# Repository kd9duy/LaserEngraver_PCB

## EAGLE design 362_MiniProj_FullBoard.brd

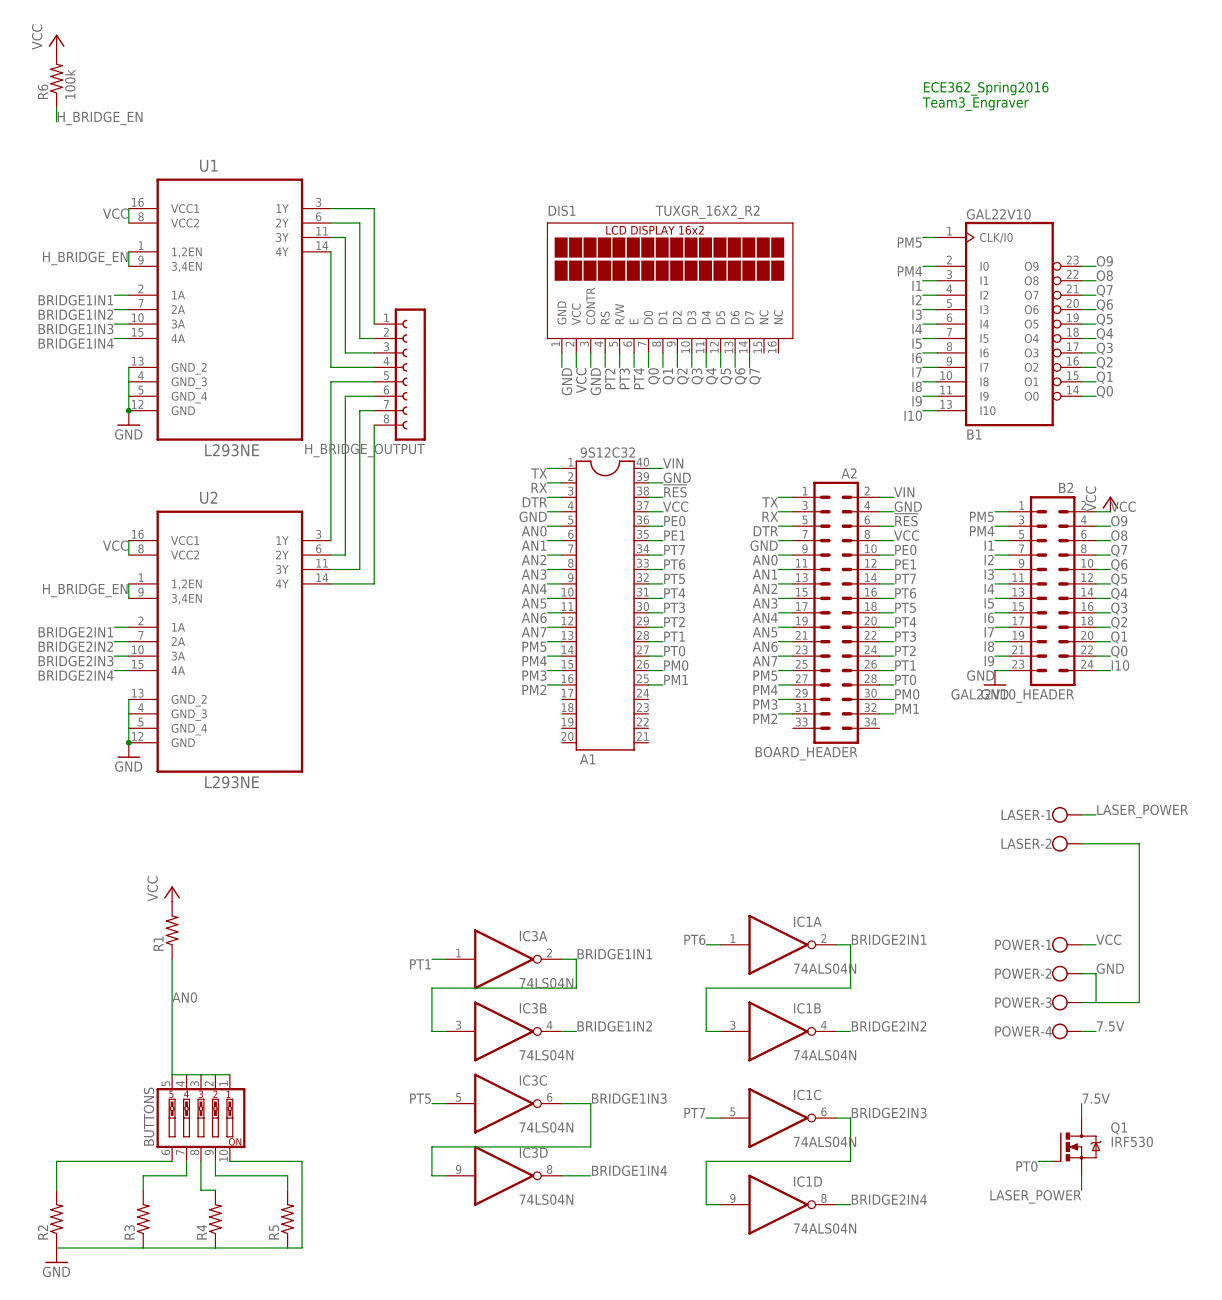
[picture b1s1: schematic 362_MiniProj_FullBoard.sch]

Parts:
9S12C32: A1; DIL40
BOARD_HEADER: A2; MA17-2
BUTTONS: SW_DIP-5; EDG-05
DIS1: TUXGR_16X2_R2
GAL22V10: B1; DIL24-3
GAL22V10_HEADER: B2; MA12-2
H_BRIDGE_OUTPUT: FE08-1; FE08
IC1: 74ALS04N; DIL14
IC3: 74LS04N; DIL14
LASER: W237-102
POWER: W239-104
Q1: IRF530; TO220BV
R1, R2, R3, R4, R5: R-US_0207/10; 0207/10
R6: 100k; 0207/10
U1, U2: L293NE; DIP254P762X508-16

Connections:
7.5V: POWER.4, Q1.D
!RES: 9S12C32.38, BOARD_HEADER.6
AN0: 9S12C32.5, BOARD_HEADER.9, BUTTONS.1, BUTTONS.2, BUTTONS.3, BUTTONS.4, BUTTONS.5, R1.1
AN1: 9S12C32.6, BOARD_HEADER.11
AN2: 9S12C32.7, BOARD_HEADER.13
AN3: 9S12C32.8, BOARD_HEADER.15
AN4: 9S12C32.9, BOARD_HEADER.17
AN5: 9S12C32.10, BOARD_HEADER.19
AN6: 9S12C32.11, BOARD_HEADER.21
AN7: 9S12C32.12, BOARD_HEADER.23
BRIDGE1IN1: IC3.2 (O), IC3.3 (I), U1.2 (1A)
BRIDGE1IN2: IC3.4 (O), U1.7 (2A)
BRIDGE1IN3: IC3.6 (O), IC3.9 (I), U1.10 (3A)
BRIDGE1IN4: IC3.8 (O), U1.15 (4A)
BRIDGE2IN1: IC1.2 (O), IC1.3 (I), U2.2 (1A)
BRIDGE2IN2: IC1.4 (O), U2.7 (2A)
BRIDGE2IN3: IC1.6 (O), IC1.9 (I), U2.10 (3A)
BRIDGE2IN4: IC1.8 (O), U2.15 (4A)
DTR: 9S12C32.3, BOARD_HEADER.5
GND: 9S12C32.4, 9S12C32.39, BOARD_HEADER.4, BOARD_HEADER.7, BUTTONS.10, DIS1.1 (GND), DIS1.3 (CONTR), GAL22V10.12 (GND), GAL22V10_HEADER.23, IC1.7 (GND), IC3.7 (GND), LASER.2, POWER.2, POWER.3, R2.1, R3.1, R4.1, R5.1, U1.4 (GND_3), U1.5 (GND_4), U1.12 (GND), U1.13 (GND_2), U2.4 (GND_3), U2.5 (GND_4), U2.12 (GND), U2.13 (GND_2)
H_BRIDGE_EN: R6.1, U1.1 (1,2EN), U1.9 (3,4EN), U2.1 (1,2EN), U2.9 (3,4EN)
I1: GAL22V10.3 (I1), GAL22V10_HEADER.5
I2: GAL22V10.4 (I2), GAL22V10_HEADER.7
I3: GAL22V10.5 (I3), GAL22V10_HEADER.9
I4: GAL22V10.6 (I4), GAL22V10_HEADER.11
I5: GAL22V10.7 (I5), GAL22V10_HEADER.13
I6: GAL22V10.8 (I6), GAL22V10_HEADER.15
I7: GAL22V10.9 (I7), GAL22V10_HEADER.17
I8: GAL22V10.10 (I8), GAL22V10_HEADER.19
I9: GAL22V10.11 (I9), GAL22V10_HEADER.21
I10: GAL22V10.13 (I10), GAL22V10_HEADER.24
LASER_POWER: LASER.1, Q1.S
unnamed: BUTTONS.6, R2.2
unnamed: BUTTONS.7, R3.2
unnamed: BUTTONS.8, R4.2
unnamed: BUTTONS.9, R5.2
unnamed: H_BRIDGE_OUTPUT.4, U1.14 (4Y)
unnamed: H_BRIDGE_OUTPUT.3, U1.11 (3Y)
unnamed: H_BRIDGE_OUTPUT.2, U1.6 (2Y)
unnamed: H_BRIDGE_OUTPUT.1, U1.3 (1Y)
unnamed: H_BRIDGE_OUTPUT.5, U2.3 (1Y)
unnamed: H_BRIDGE_OUTPUT.6, U2.6 (2Y)
unnamed: H_BRIDGE_OUTPUT.7, U2.11 (3Y)
unnamed: H_BRIDGE_OUTPUT.8, U2.14 (4Y)
O8: GAL22V10.22 (O8), GAL22V10_HEADER.6
O9: GAL22V10.23 (O9), GAL22V10_HEADER.4
PE0: 9S12C32.36, BOARD_HEADER.10
PE1: 9S12C32.35, BOARD_HEADER.12
PM0: 9S12C32.26, BOARD_HEADER.30
PM1: 9S12C32.25, BOARD_HEADER.32
PM2: 9S12C32.16, BOARD_HEADER.31
PM3: 9S12C32.15, BOARD_HEADER.29
PM4: 9S12C32.14, BOARD_HEADER.27, GAL22V10.2 (I0), GAL22V10_HEADER.3
PM5: 9S12C32.13, BOARD_HEADER.25, GAL22V10.1 (CLK/I0), GAL22V10_HEADER.1
PT0: 9S12C32.27, BOARD_HEADER.28, Q1.G
PT1: 9S12C32.28, BOARD_HEADER.26, IC3.1 (I)
PT2: 9S12C32.29, BOARD_HEADER.24, DIS1.4 (RS)
PT3: 9S12C32.30, BOARD_HEADER.22, DIS1.5 (R/W)
PT4: 9S12C32.31, BOARD_HEADER.20, DIS1.6 (E)
PT5: 9S12C32.32, BOARD_HEADER.18, IC3.5 (I)
PT6: 9S12C32.33, BOARD_HEADER.16, IC1.1 (I)
PT7: 9S12C32.34, BOARD_HEADER.14, IC1.5 (I)
Q0: DIS1.7 (D0), GAL22V10.14 (O0), GAL22V10_HEADER.22
Q1: DIS1.8 (D1), GAL22V10.15 (O1), GAL22V10_HEADER.20
Q2: DIS1.9 (D2), GAL22V10.16 (O2), GAL22V10_HEADER.18
Q3: DIS1.10 (D3), GAL22V10.17 (O3), GAL22V10_HEADER.16
Q4: DIS1.11 (D4), GAL22V10.18 (O4), GAL22V10_HEADER.14
Q5: DIS1.12 (D5), GAL22V10.19 (O5), GAL22V10_HEADER.12
Q6: DIS1.13 (D6), GAL22V10.20 (O6), GAL22V10_HEADER.10
Q7: DIS1.14 (D7), GAL22V10.21 (O7), GAL22V10_HEADER.8
RX: 9S12C32.2, BOARD_HEADER.3
TX: 9S12C32.1, BOARD_HEADER.1
VCC: 9S12C32.37, BOARD_HEADER.8, DIS1.2 (VCC), GAL22V10.24 (VCC), GAL22V10_HEADER.2, IC1.14 (VCC), IC3.14 (VCC), POWER.1, R1.2, R6.2, U1.8 (VCC2), U1.16 (VCC1), U2.8 (VCC2), U2.16 (VCC1)
VIN: 9S12C32.40, BOARD_HEADER.2

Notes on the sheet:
ECE362_Spring2016 Team3_Engraver

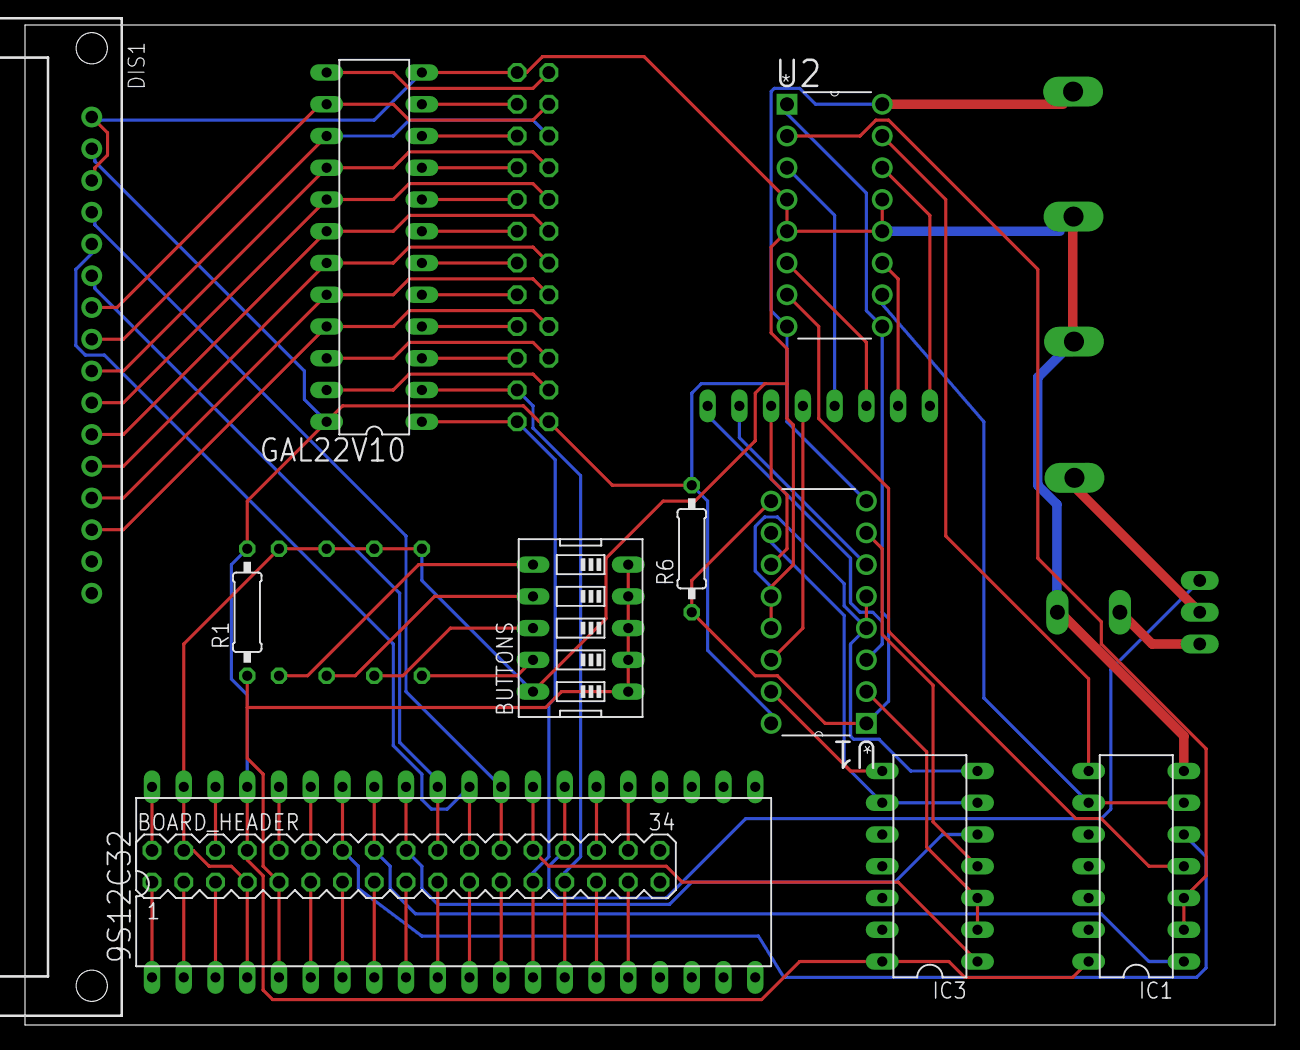
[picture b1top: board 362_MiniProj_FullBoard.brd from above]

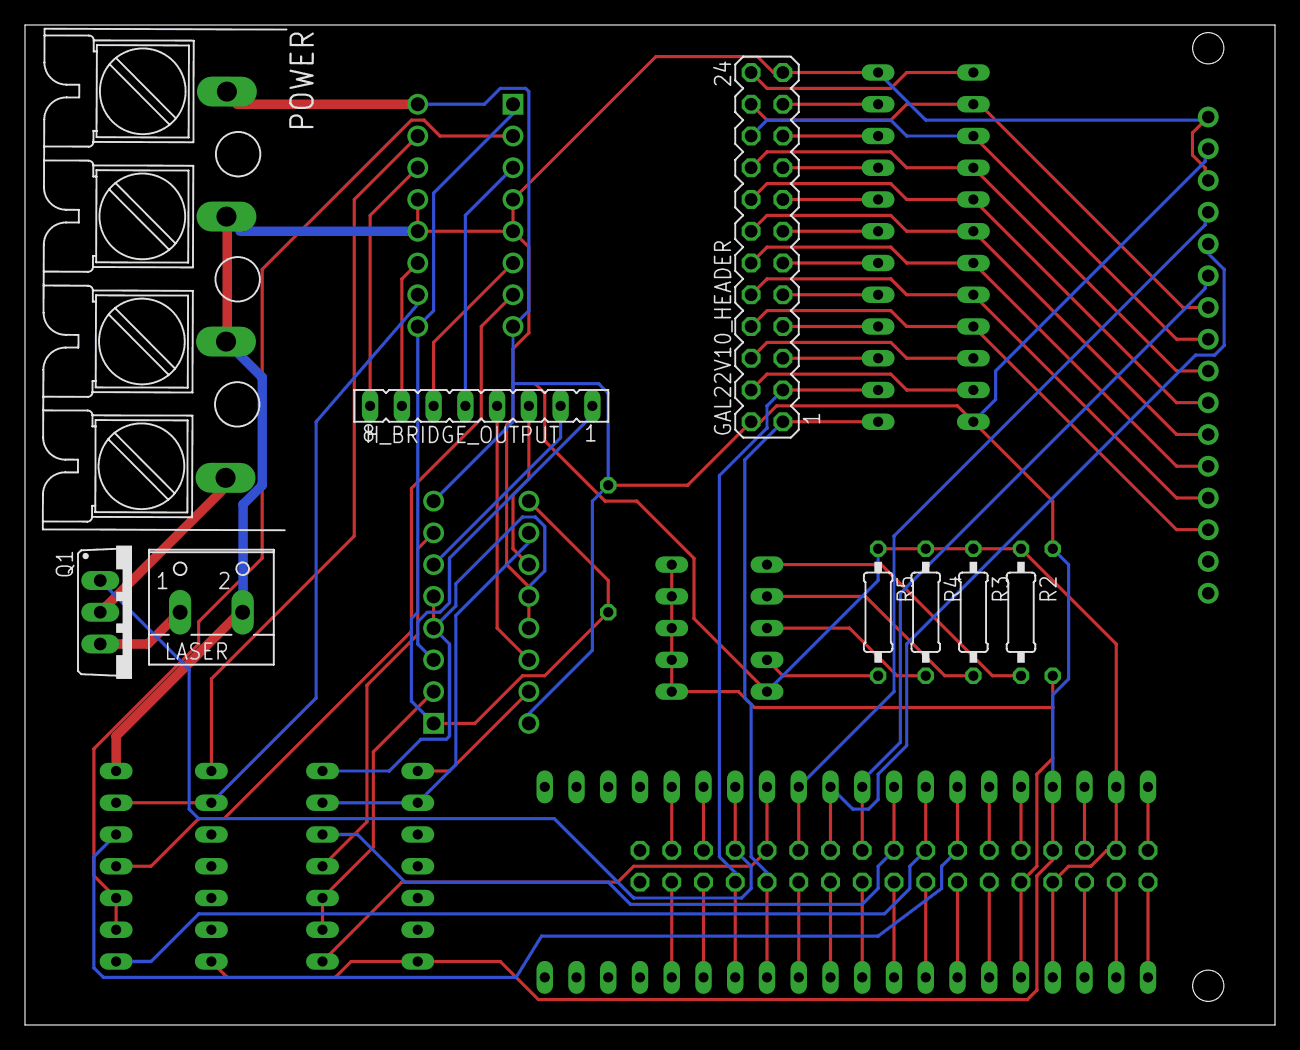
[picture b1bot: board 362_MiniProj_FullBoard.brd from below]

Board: 2 copper layers, 100.0 x 80.0 mm, 20 parts (9 on the bottom side), 74 nets.

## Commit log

2016-05-05 Added files via upload
